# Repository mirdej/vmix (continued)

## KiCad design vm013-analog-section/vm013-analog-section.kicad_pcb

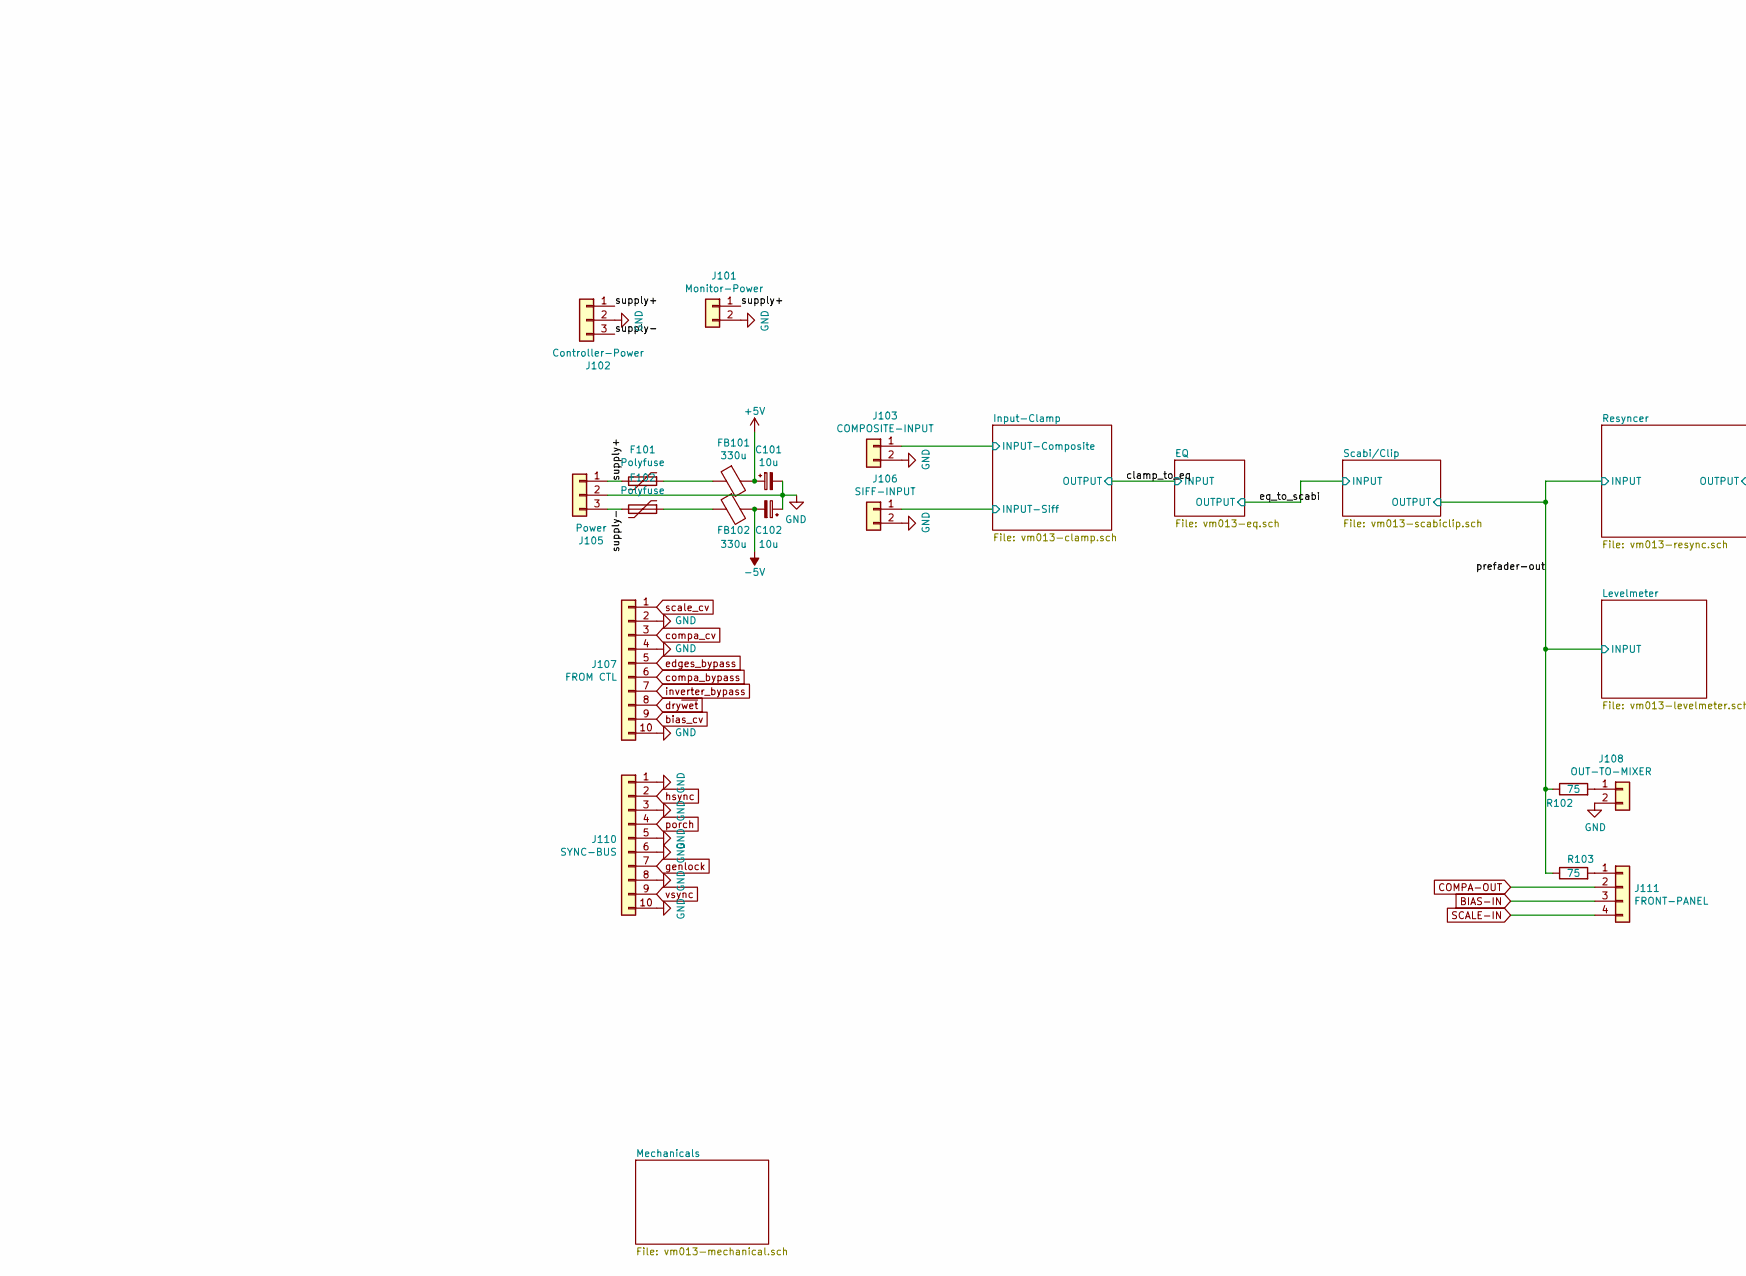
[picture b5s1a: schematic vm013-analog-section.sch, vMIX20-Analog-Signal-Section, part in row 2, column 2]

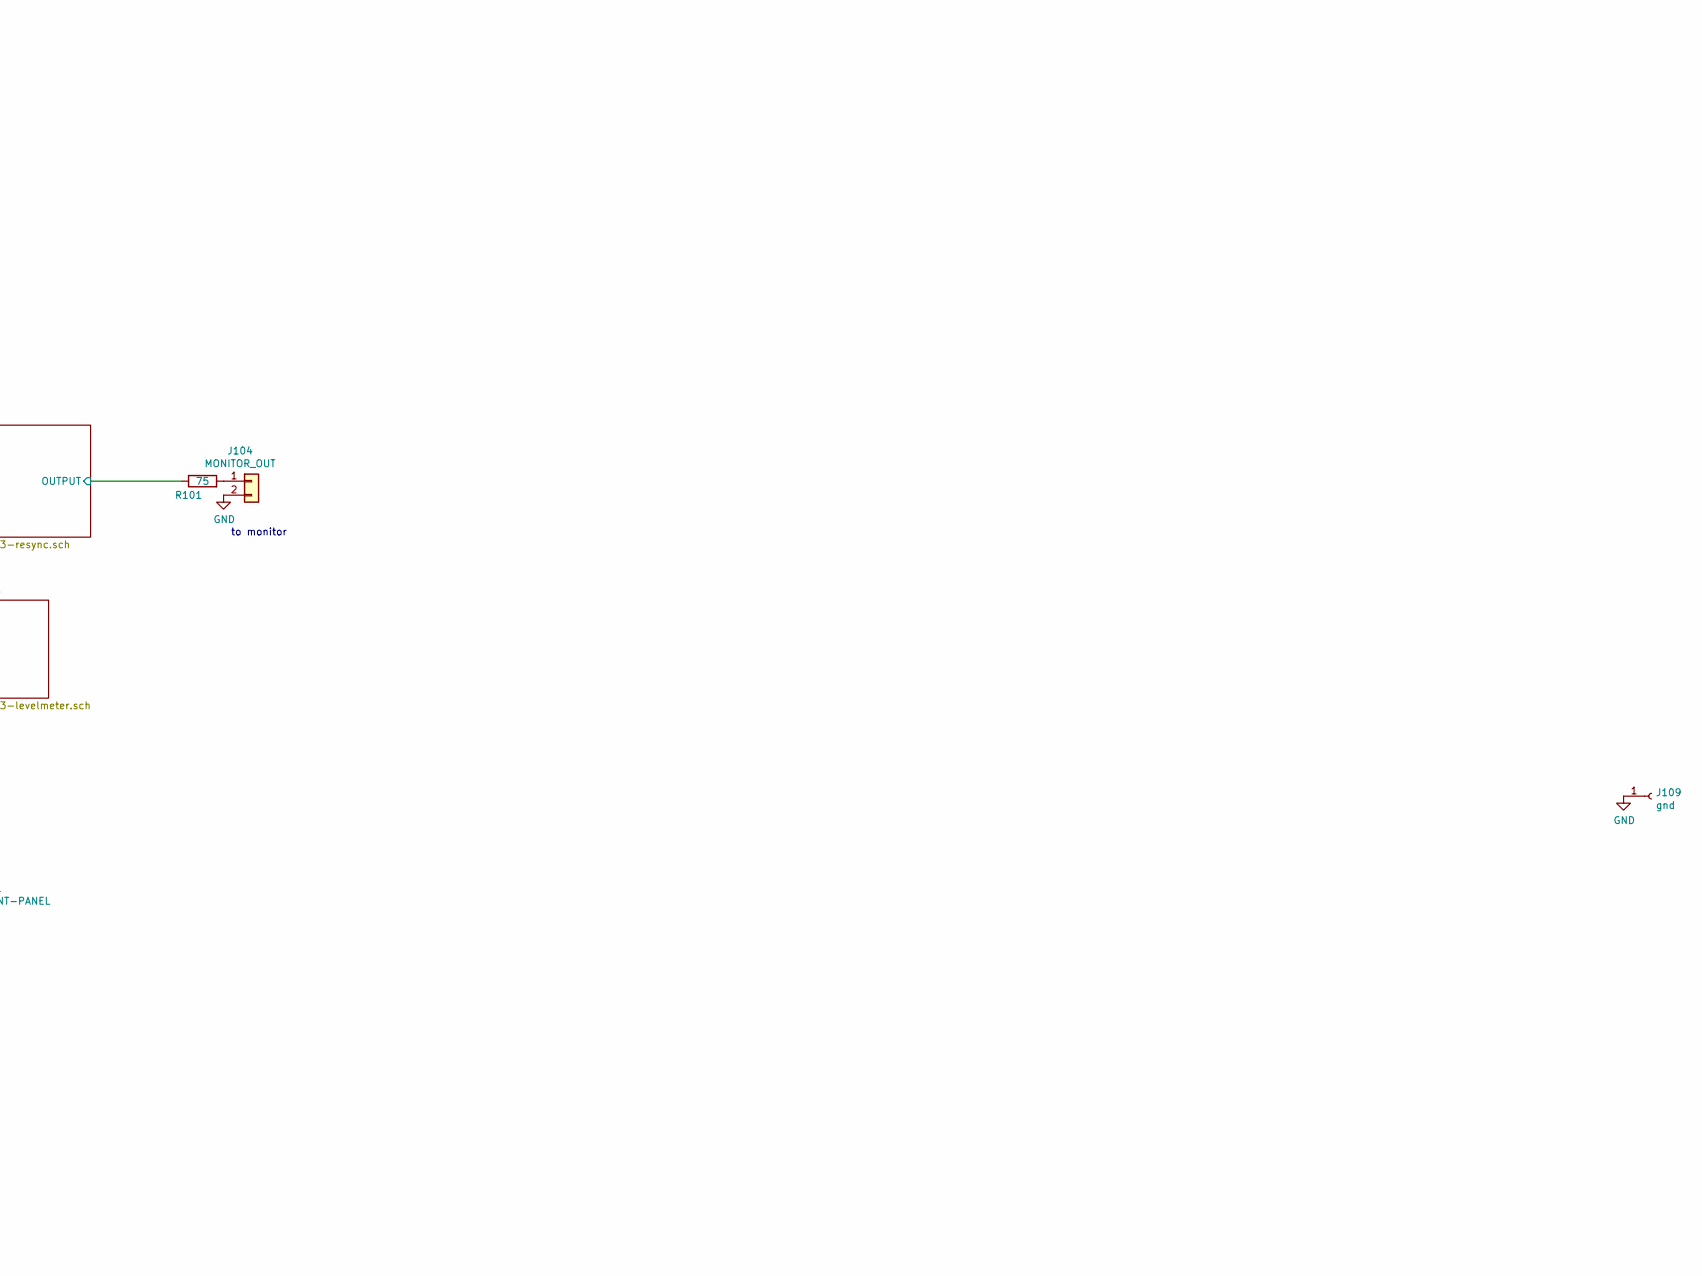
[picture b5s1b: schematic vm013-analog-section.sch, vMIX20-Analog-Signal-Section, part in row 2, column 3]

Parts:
C101, C102: 10u; CP_EIA-3528-21_Kemet-B_Pad1.50x2.35mm_HandSolder
F101, F102: Polyfuse; Fuse_0805_2012Metric
FB101, FB102: 330u; L_0805_2012Metric_Pad1.15x1.40mm_HandSolder
J101: Monitor-Power; Molex_KK-254_AE-6410-02A_1x02_P2.54mm_Vertical
J102: Controller-Power; Molex_KK-254_AE-6410-03A_1x03_P2.54mm_Vertical
J103: COMPOSITE-INPUT; Molex_KK-254_AE-6410-02A_1x02_P2.54mm_Vertical
J104: MONITOR_OUT; Molex_KK-254_AE-6410-02A_1x02_P2.54mm_Vertical
J105: Power; Molex_KK-254_AE-6410-03A_1x03_P2.54mm_Vertical
J106: SIFF-INPUT; Molex_KK-254_AE-6410-02A_1x02_P2.54mm_Vertical
J107: FROM CTL; IDC-Header_2x05_P2.54mm_Vertical
J108: OUT-TO-MIXER; Molex_KK-254_AE-6410-02A_1x02_P2.54mm_Vertical
J109: gnd; Solderpad_1mm
J110: SYNC-BUS; IDC-Header_2x05_P2.54mm_Vertical
J111: FRONT-PANEL; Molex_KK-254_AE-6410-04A_1x04_P2.54mm_Vertical
R101, R102, R103: 75; R_0805_2012Metric_Pad1.15x1.40mm_HandSolder

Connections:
+5V: C101.1, FB101.2; also elsewhere on the board
-5V: C102.2, FB102.2; also elsewhere on the board
/Input-Clamp/INPUT-Composite: J103.1; also elsewhere on the board
/Input-Clamp/INPUT-Siff: J106.1; also elsewhere on the board
/Resyncer/OUTPUT: R101.1; also elsewhere on the board
/prefader-out: R102.1, R103.1; also elsewhere on the board
/supply+: F101.2, J101.1, J102.1, J105.1
/supply-: F102.2, J102.3, J105.3
BIAS-IN: J111.3; also elsewhere on the board
COMPA-OUT: J111.2; also elsewhere on the board
GND: C101.2, C102.1, J101.2, J102.2, J103.2, J104.2, J105.2, J106.2, J107.2, J107.4, J107.10, J108.2, J109.1, J110.1, J110.3, J110.5, J110.6, J110.8, J110.10; also elsewhere on the board
unnamed: F101.1, FB101.1
unnamed: F102.1, FB102.1
unnamed: J104.1, R101.2
unnamed: J108.1, R102.2
unnamed: J111.1, R103.2
SCALE-IN: J111.4; also elsewhere on the board
bias_cv: J107.9; also elsewhere on the board
compa_bypass: J107.6; also elsewhere on the board
compa_cv: J107.3; also elsewhere on the board
dry~wet~: J107.8; also elsewhere on the board
edges_bypass: J107.5; also elsewhere on the board
genlock: J110.7; also elsewhere on the board
hsync: J110.2; also elsewhere on the board
inverter_bypass: J107.7; also elsewhere on the board
porch: J110.4; also elsewhere on the board
scale_cv: J107.1; also elsewhere on the board
vsync: J110.9; also elsewhere on the board

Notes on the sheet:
to monitor

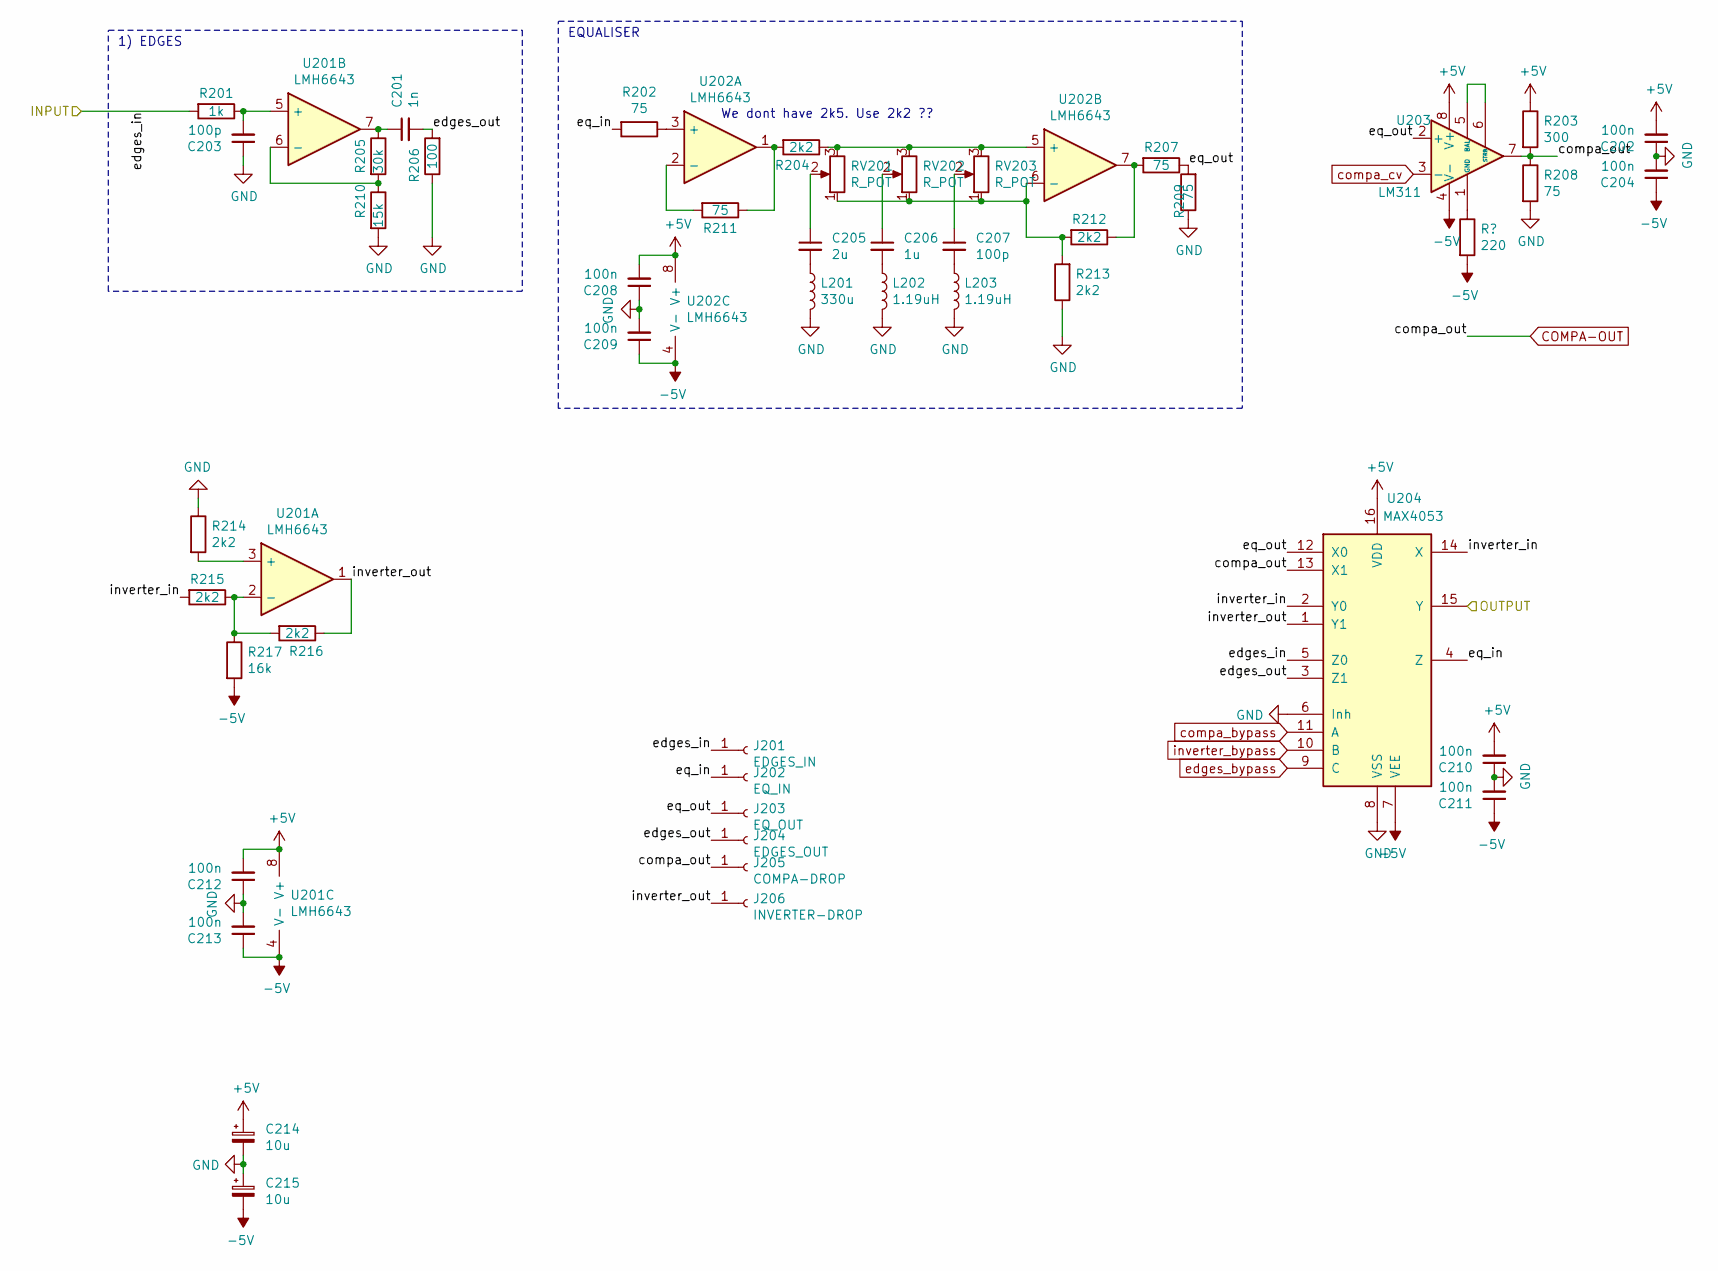
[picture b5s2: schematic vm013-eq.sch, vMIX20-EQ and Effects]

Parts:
C201: 1n; C_0805_2012Metric_Pad1.15x1.40mm_HandSolder
C202, C204, C208, C209, C210, C211, C212, C213: 100n; C_0603_1608Metric_Pad1.05x0.95mm_HandSolder
C203, C207: 100p; C_0805_2012Metric_Pad1.15x1.40mm_HandSolder
C205: 2u; C_1206_3216Metric_Pad1.42x1.75mm_HandSolder
C206: 1u; C_1206_3216Metric_Pad1.42x1.75mm_HandSolder
C214, C215: 10u; CP_EIA-3528-21_Kemet-B_Pad1.50x2.35mm_HandSolder
J201: EDGES_IN; Solderpad_1mm
J202: EQ_IN; Solderpad_1mm
J203: EQ_OUT; Solderpad_1mm
J204: EDGES_OUT; Solderpad_1mm
J205: COMPA-DROP; Solderpad_1mm
J206: INVERTER-DROP; Solderpad_1mm
L201: 330u; L_1210_3225Metric_Pad1.42x2.65mm_HandSolder
L202, L203: 1.19uH; L_1210_3225Metric_Pad1.42x2.65mm_HandSolder
R201: 1k; R_0805_2012Metric_Pad1.15x1.40mm_HandSolder
R202, R207, R208, R209, R211: 75; R_0805_2012Metric_Pad1.15x1.40mm_HandSolder
R203: 300; R_0805_2012Metric_Pad1.15x1.40mm_HandSolder
R204, R212, R213, R214, R215, R216: 2k2; R_0805_2012Metric_Pad1.15x1.40mm_HandSolder
R205: 30k; R_0805_2012Metric_Pad1.15x1.40mm_HandSolder
R206: 100; R_0805_2012Metric_Pad1.15x1.40mm_HandSolder
R210: 15k; R_0805_2012Metric_Pad1.15x1.40mm_HandSolder
R217: 16k; R_0805_2012Metric_Pad1.15x1.40mm_HandSolder
RV201, RV202, RV203: R_POT; Potentiometer_Alps_RK09K_Single_Horizontal
U201, U202: LMH6643; SOIC-8_3.9x4.9mm_P1.27mm
U203: LM311; SOIC-8_3.9x4.9mm_P1.27mm
U204: MAX4053; SOP-16_4.55x10.3mm_P1.27mm

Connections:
+5V: C202.2, C208.2, C210.2, C212.2, C214.1, R203.1, U201.8 (V+), U202.8 (V+), U203.8 (V+), U204.16 (VDD); also elsewhere on the board
-5V: C204.1, C209.1, C211.1, C213.1, C215.2, R217.2, U201.4 (V-), U202.4 (V-), U203.4 (V-), U204.7 (VEE); also elsewhere on the board
/EQ/edges_out: C201.2, J204.1, R206.2, U204.3 (Z1)
/EQ/eq_in: J202.1, R202.2, U204.4 (Z)
/EQ/eq_out: J203.1, R207.1, R209.2, U203.2 (+), U204.12 (X0)
/EQ/inverter_in: R215.2, U204.2 (Y0), U204.14 (X)
/EQ/inverter_out: J206.1, R216.1, U201.1, U204.1 (Y1)
/clamp_to_eq: J201.1, R201.2, U204.5 (Z0); also elsewhere on the board
/eq_to_scabi: U204.15 (Y); also elsewhere on the board
COMPA-OUT: J205.1, R203.2, R208.1, U203.7, U204.13 (X1); also elsewhere on the board
GND: C202.1, C203.1, C204.2, C208.1, C209.2, C210.1, C211.2, C212.1, C213.2, C214.2, C215.1, L201.2, L202.2, L203.2, R206.1, R208.2, R209.1, R210.2, R213.1, R214.1, U203.1 (GND), U204.6 (Inh), U204.8 (VSS); also elsewhere on the board
unnamed: C201.1, R205.1, U201.7
unnamed: C203.2, R201.1, U201.5 (+)
unnamed: C205.1, RV201.2
unnamed: C205.2, L201.1
unnamed: C206.1, RV202.2
unnamed: C206.2, L202.1
unnamed: C207.1, RV203.2
unnamed: C207.2, L203.1
unnamed: R202.1, U202.3 (+)
unnamed: R204.1, RV201.3, RV202.3, RV203.3, U202.5 (+)
unnamed: R204.2, R211.1, U202.1
unnamed: R205.2, R210.1, U201.6 (-)
unnamed: R207.2, R212.1, U202.7
unnamed: R211.2, U202.2 (-)
unnamed: R212.2, R213.2, RV201.1, RV202.1, RV203.1, U202.6 (-)
unnamed: R214.2, U201.3 (+)
unnamed: R215.1, R216.2, R217.1, U201.2 (-)
unnamed: U203.5 (BAL), U203.6 (STRB)
compa_bypass: U204.11 (A); also elsewhere on the board
compa_cv: U203.3 (-); also elsewhere on the board
edges_bypass: U204.9 (C); also elsewhere on the board
inverter_bypass: U204.10 (B); also elsewhere on the board

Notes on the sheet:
EQUALISER
We dont have 2k5. Use 2k2 ??
1) EDGES

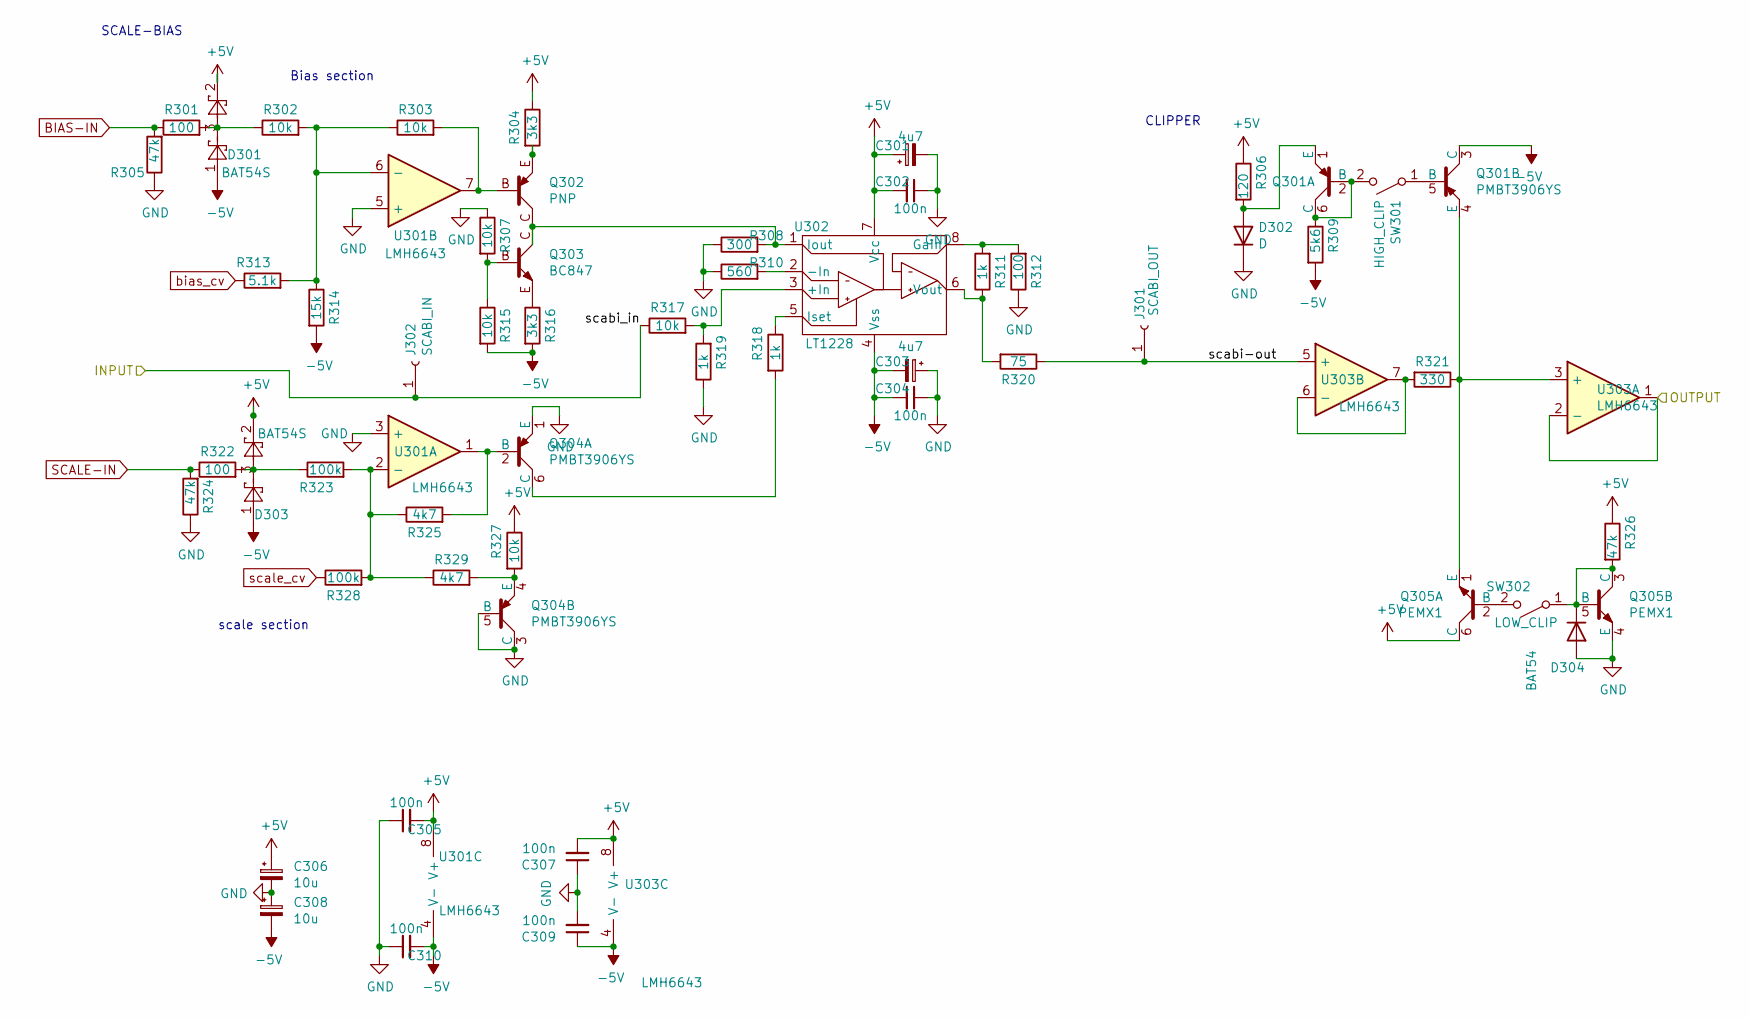
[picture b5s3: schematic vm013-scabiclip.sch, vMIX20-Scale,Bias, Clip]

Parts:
C301, C303: 4u7; CP_EIA-3528-21_Kemet-B_Pad1.50x2.35mm_HandSolder
C302, C304, C305, C307, C309, C310: 100n; C_0603_1608Metric_Pad1.05x0.95mm_HandSolder
C306, C308: 10u; CP_EIA-3528-21_Kemet-B_Pad1.50x2.35mm_HandSolder
D301, D303: BAT54S; SOT-23
D302: D; D_MiniMELF
D304: BAT54; D_SOT-23_ANK
J301: SCABI_OUT; Solderpad_1mm
J302: SCABI_IN; Solderpad_1mm
Q301, Q304: PMBT3906YS; SOT-363_SC-70-6_Handsoldering
Q302: PNP; SOT-23_BEC
Q303: BC847; SOT-23_BEC
Q305: PEMX1; SOT-666
R301, R312, R322: 100; R_0805_2012Metric_Pad1.15x1.40mm_HandSolder
R302, R303, R307, R315, R317, R327: 10k; R_0805_2012Metric_Pad1.15x1.40mm_HandSolder
R304, R316: 3k3; R_0805_2012Metric_Pad1.15x1.40mm_HandSolder
R305, R324, R326: 47k; R_0805_2012Metric_Pad1.15x1.40mm_HandSolder
R306: 120; R_0805_2012Metric_Pad1.15x1.40mm_HandSolder
R308: 300; R_0805_2012Metric_Pad1.15x1.40mm_HandSolder
R309: 5k6; R_0805_2012Metric_Pad1.15x1.40mm_HandSolder
R310: 560; R_0805_2012Metric_Pad1.15x1.40mm_HandSolder
R311, R318, R319: 1k; R_0805_2012Metric_Pad1.15x1.40mm_HandSolder
R313: 5.1k; R_0805_2012Metric_Pad1.15x1.40mm_HandSolder
R314: 15k; R_0805_2012Metric_Pad1.15x1.40mm_HandSolder
R320: 75; R_0805_2012Metric_Pad1.15x1.40mm_HandSolder
R321: 330; R_0805_2012Metric_Pad1.15x1.40mm_HandSolder
R323, R328: 100k; R_0805_2012Metric_Pad1.15x1.40mm_HandSolder
R325, R329: 4k7; R_0805_2012Metric_Pad1.15x1.40mm_HandSolder
SW301: HIGH_CLIP; Molex_KK-254_AE-6410-02A_1x02_P2.54mm_Vertical
SW302: LOW_CLIP; Molex_KK-254_AE-6410-02A_1x02_P2.54mm_Vertical
U301, U303: LMH6643; SOIC-8_3.9x4.9mm_P1.27mm
U302: LT1228; SOIC-8_3.9x4.9mm_P1.27mm

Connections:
+5V: C301.1, C302.2, C305.2, C306.1, C307.2, D301.2, D303.2, Q305.6 (C), R304.1, R306.1, R326.1, R327.1, U301.8 (V+), U302.7 (Vcc), U303.8 (V+); also elsewhere on the board
-5V: C303.2, C304.2, C308.2, C309.1, C310.2, D301.1, D303.1, Q301.3 (C), R309.2, R314.2, R315.2, R316.2, U301.4 (V-), U302.4 (Vss), U303.4 (V-); also elsewhere on the board
/Scabi/Clip/scabi-out: J301.1, R320.1, U303.5 (+)
/eq_to_scabi: J302.1, R317.1; also elsewhere on the board
/prefader-out: U303.1, U303.2 (-); also elsewhere on the board
BIAS-IN: R301.1, R305.2; also elsewhere on the board
GND: C301.2, C302.1, C303.1, C304.1, C305.1, C306.2, C307.1, C308.1, C309.2, C310.1, D302.1 (K), D304.2 (A), Q304.1 (E), Q304.3 (C), Q304.5 (B), Q305.4 (E), R305.1, R307.1, R308.1, R310.1, R312.1, R319.1, R324.1, U301.3 (+), U301.5 (+); also elsewhere on the board
unnamed: D301.3, R301.2, R302.1
unnamed: D302.2 (A), Q301.1 (E), R306.2
unnamed: D303.3, R322.2, R323.1
unnamed: D304.1 (K), Q305.3 (C), Q305.5 (B), R326.2, SW302.1 (A)
unnamed: Q301.2 (B), Q301.6 (C), R309.1, SW301.2 (B)
unnamed: Q301.4 (E), Q305.1 (E), R321.1, U303.3 (+)
unnamed: Q301.5 (B), SW301.1 (A)
unnamed: Q302.B, R303.2, U301.7
unnamed: Q302.C, Q303.C, R308.2, U302.1 (Iout)
unnamed: Q302.E, R304.2
unnamed: Q303.B, R307.2, R315.1
unnamed: Q303.E, R316.1
unnamed: Q304.2 (B), R325.2, U301.1
unnamed: Q304.4 (E), R327.2, R329.2
unnamed: Q304.6 (C), R318.2
unnamed: Q305.2 (B), SW302.2 (B)
unnamed: R302.2, R303.1, R313.2, R314.1, U301.6 (-)
unnamed: R310.2, U302.2 (-In)
unnamed: R311.1, R320.2, U302.6 (Vout)
unnamed: R311.2, R312.2, U302.8 (Gain)
unnamed: R317.2, R319.2, U302.3 (+In)
unnamed: R318.1, U302.5 (Iset)
unnamed: R321.2, U303.6 (-), U303.7
unnamed: R323.2, R325.1, R328.2, R329.1, U301.2 (-)
SCALE-IN: R322.1, R324.2; also elsewhere on the board
bias_cv: R313.1; also elsewhere on the board
scale_cv: R328.1; also elsewhere on the board

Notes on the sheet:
Bias section
scale section
SCALE-BIAS
CLIPPER

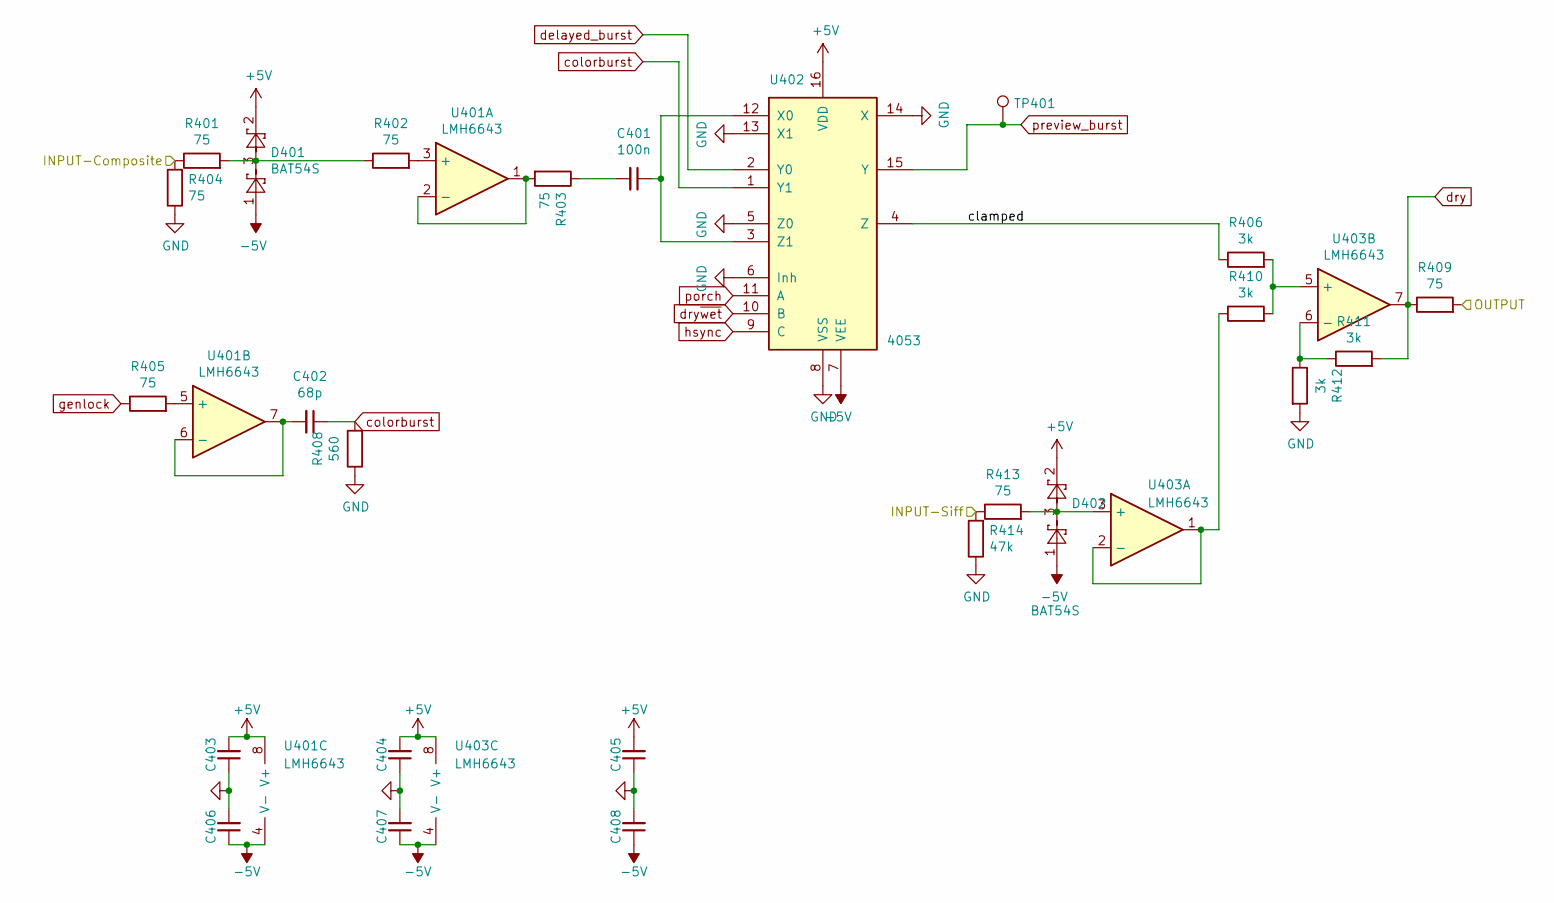
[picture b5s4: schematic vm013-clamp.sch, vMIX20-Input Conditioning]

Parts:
C401, C403, C404, C405, C406, C407, C408: 100n; C_0603_1608Metric_Pad1.05x0.95mm_HandSolder
C402: 68p; C_1206_3216Metric_Pad1.42x1.75mm_HandSolder
D401, D402: BAT54S; SOT-23
R401, R402, R403, R404, R405, R409, R413: 75; R_0805_2012Metric_Pad1.15x1.40mm_HandSolder
R406, R410, R411, R412: 3k; R_0805_2012Metric_Pad1.15x1.40mm_HandSolder
R408: 560; R_0805_2012Metric_Pad1.15x1.40mm_HandSolder
R414: 47k; R_0805_2012Metric_Pad1.15x1.40mm_HandSolder
TP401: TestPoint; Solderpad_1mm
U401, U403: LMH6643; SOIC-8_3.9x4.9mm_P1.27mm
U402: 4053; SOIC-16_3.9x9.9mm_P1.27mm

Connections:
+5V: C403.2, C404.2, C405.2, D401.2, D402.2, U401.8 (V+), U402.16 (VDD), U403.8 (V+); also elsewhere on the board
-5V: C406.1, C407.1, C408.1, D401.1, D402.1, U401.4 (V-), U402.7 (VEE), U403.4 (V-); also elsewhere on the board
/Input-Clamp/INPUT-Composite: R401.1, R404.2; also elsewhere on the board
/Input-Clamp/INPUT-Siff: R413.1, R414.2; also elsewhere on the board
/Input-Clamp/clamped: R406.1, U402.4 (Z)
/clamp_to_eq: R409.2; also elsewhere on the board
GND: C403.1, C404.1, C405.1, C406.2, C407.2, C408.2, R404.1, R408.1, R412.2, R414.1, U402.5 (Z0), U402.6 (Inh), U402.8 (VSS), U402.13 (X1), U402.14 (X); also elsewhere on the board
unnamed: C401.1, U402.3 (Z1), U402.12 (X0)
unnamed: C401.2, R403.1
unnamed: C402.2, U401.6 (-), U401.7
unnamed: D401.3, R401.2, R402.1
unnamed: D402.3, R413.2, U403.3 (+)
unnamed: R402.2, U401.3 (+)
unnamed: R403.2, U401.1, U401.2 (-)
unnamed: R405.2, U401.5 (+)
unnamed: R406.2, R410.2, U403.5 (+)
unnamed: R410.1, U403.1, U403.2 (-)
unnamed: R411.1, R412.1, U403.6 (-)
colorburst: C402.1, R408.2, U402.1 (Y1); also elsewhere on the board
delayed_burst: U402.2 (Y0); also elsewhere on the board
dry: R409.1, R411.2, U403.7; also elsewhere on the board
dry~wet~: U402.10 (B); also elsewhere on the board
genlock: R405.1; also elsewhere on the board
hsync: U402.9 (C); also elsewhere on the board
porch: U402.11 (A); also elsewhere on the board
preview_burst: TP401.1, U402.15 (Y); also elsewhere on the board

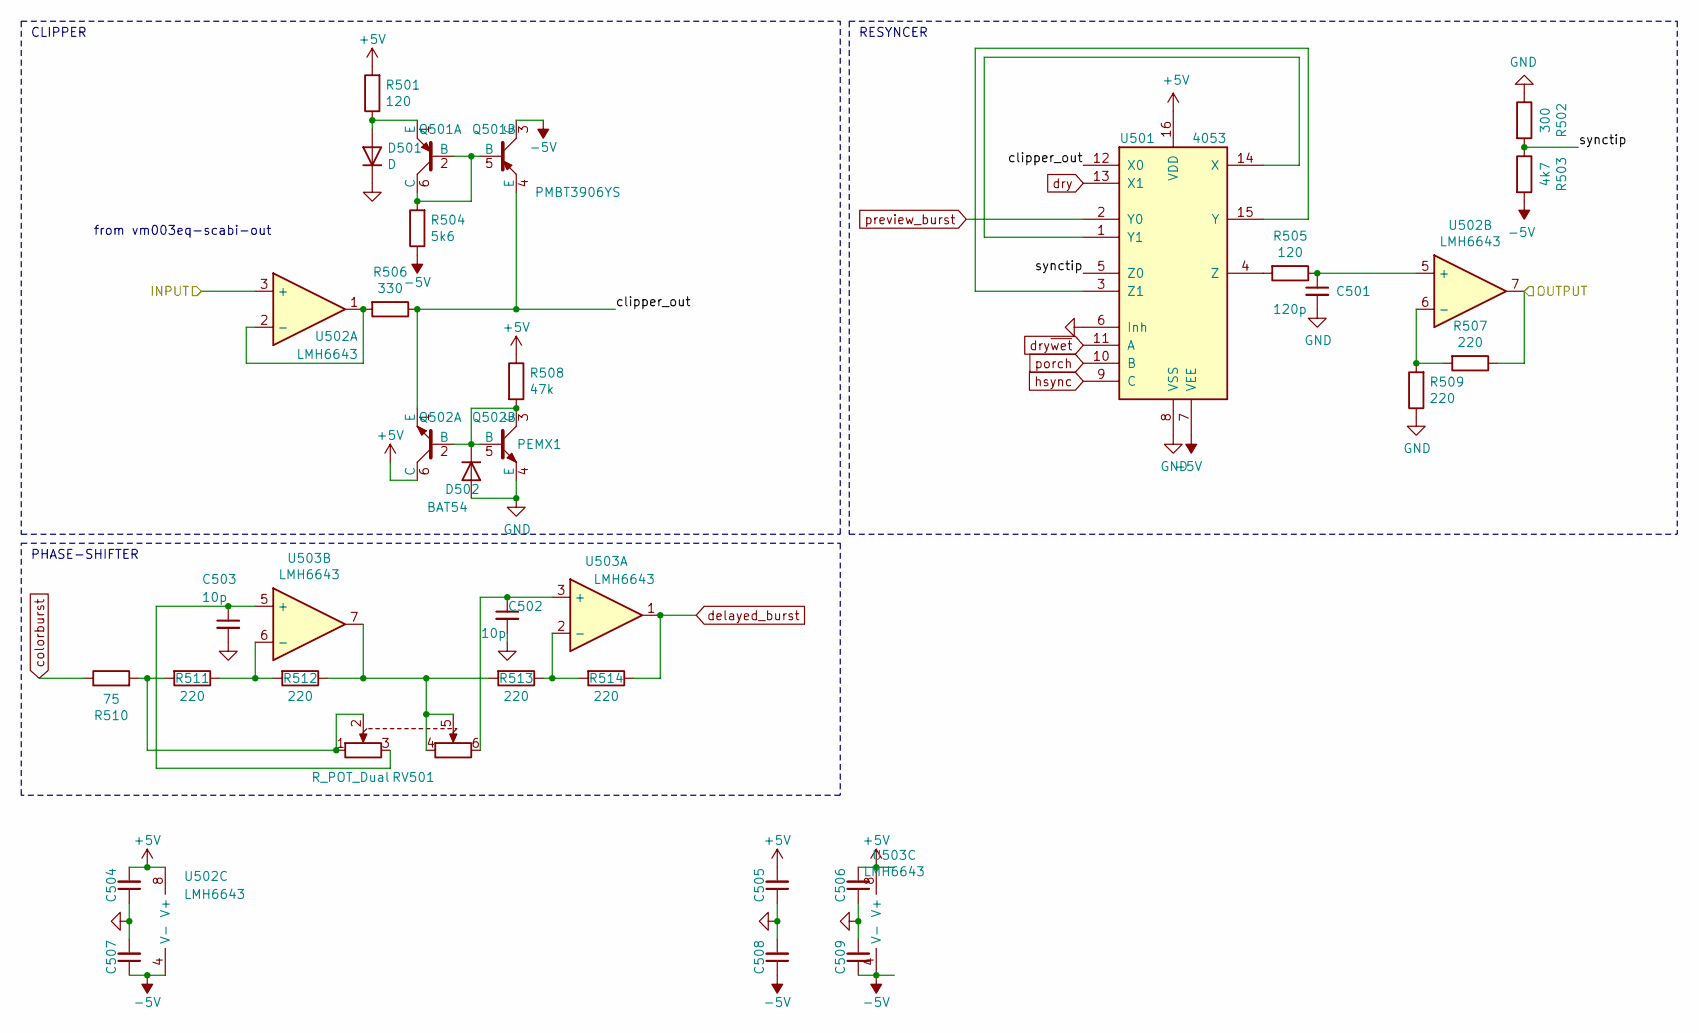
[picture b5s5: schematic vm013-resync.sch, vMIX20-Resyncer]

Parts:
C501: 120p; C_0805_2012Metric_Pad1.15x1.40mm_HandSolder
C502, C503: 10p; C_0805_2012Metric_Pad1.15x1.40mm_HandSolder
C504, C505, C506, C507, C508, C509: 100n; C_0603_1608Metric_Pad1.05x0.95mm_HandSolder
D501: D; D_MiniMELF
D502: BAT54; D_SOT-23_ANK
Q501: PMBT3906YS; SOT-363_SC-70-6_Handsoldering
Q502: PEMX1; SOT-666
R501, R505: 120; R_0805_2012Metric_Pad1.15x1.40mm_HandSolder
R502: 300; R_0805_2012Metric_Pad1.15x1.40mm_HandSolder
R503: 4k7; R_0805_2012Metric_Pad1.15x1.40mm_HandSolder
R504: 5k6; R_0805_2012Metric_Pad1.15x1.40mm_HandSolder
R506: 330; R_0805_2012Metric_Pad1.15x1.40mm_HandSolder
R507, R509, R511, R512, R513, R514: 220; R_0805_2012Metric_Pad1.15x1.40mm_HandSolder
R508: 47k; R_0805_2012Metric_Pad1.15x1.40mm_HandSolder
R510: 75; R_0805_2012Metric_Pad1.15x1.40mm_HandSolder
RV501: R_POT_Dual; RK12L123
U501: 4053; SOIC-16_3.9x9.9mm_P1.27mm
U502, U503: LMH6643; SOIC-8_3.9x4.9mm_P1.27mm

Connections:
+5V: C504.2, C505.2, C506.2, Q502.6 (C), R501.2, R508.1, U501.16 (VDD), U502.8 (V+), U503.8 (V+); also elsewhere on the board
-5V: C507.1, C508.1, C509.1, Q501.3 (C), R503.2, R504.1, U501.7 (VEE), U502.4 (V-), U503.4 (V-); also elsewhere on the board
/Resyncer/OUTPUT: R507.1, U502.7; also elsewhere on the board
/Resyncer/clipper_out: Q501.4 (E), Q502.1 (E), R506.1, U501.12 (X0)
/Resyncer/synctip: R502.2, R503.1, U501.5 (Z0)
/prefader-out: U502.3 (+); also elsewhere on the board
GND: C501.2, C502.2, C503.2, C504.1, C505.1, C506.1, C507.2, C508.2, C509.2, D501.1 (K), D502.2 (A), Q502.4 (E), R502.1, R509.1, U501.6 (Inh), U501.8 (VSS); also elsewhere on the board
unnamed: C501.1, R505.1, U502.5 (+)
unnamed: C502.1, RV501.6, U503.3 (+)
unnamed: C503.1, RV501.3, U503.5 (+)
unnamed: D501.2 (A), Q501.1 (E), R501.1
unnamed: D502.1 (K), Q502.2 (B), Q502.3 (C), Q502.5 (B), R508.2
unnamed: Q501.2 (B), Q501.5 (B), Q501.6 (C), R504.2
unnamed: R505.2, U501.4 (Z)
unnamed: R506.2, U502.1, U502.2 (-)
unnamed: R507.2, R509.2, U502.6 (-)
unnamed: R510.2, R511.2, RV501.1, RV501.2
unnamed: R511.1, R512.2, U503.6 (-)
unnamed: R512.1, R513.2, RV501.4, RV501.5, U503.7
unnamed: R513.1, R514.2, U503.2 (-)
unnamed: U501.1 (Y1), U501.14 (X)
unnamed: U501.3 (Z1), U501.15 (Y)
colorburst: R510.1; also elsewhere on the board
delayed_burst: R514.1, U503.1; also elsewhere on the board
dry: U501.13 (X1); also elsewhere on the board
dry~wet~: U501.11 (A); also elsewhere on the board
hsync: U501.9 (C); also elsewhere on the board
porch: U501.10 (B); also elsewhere on the board
preview_burst: U501.2 (Y0); also elsewhere on the board

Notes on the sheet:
PHASE-SHIFTER
CLIPPER
RESYNCER
from vm003eq-scabi-out

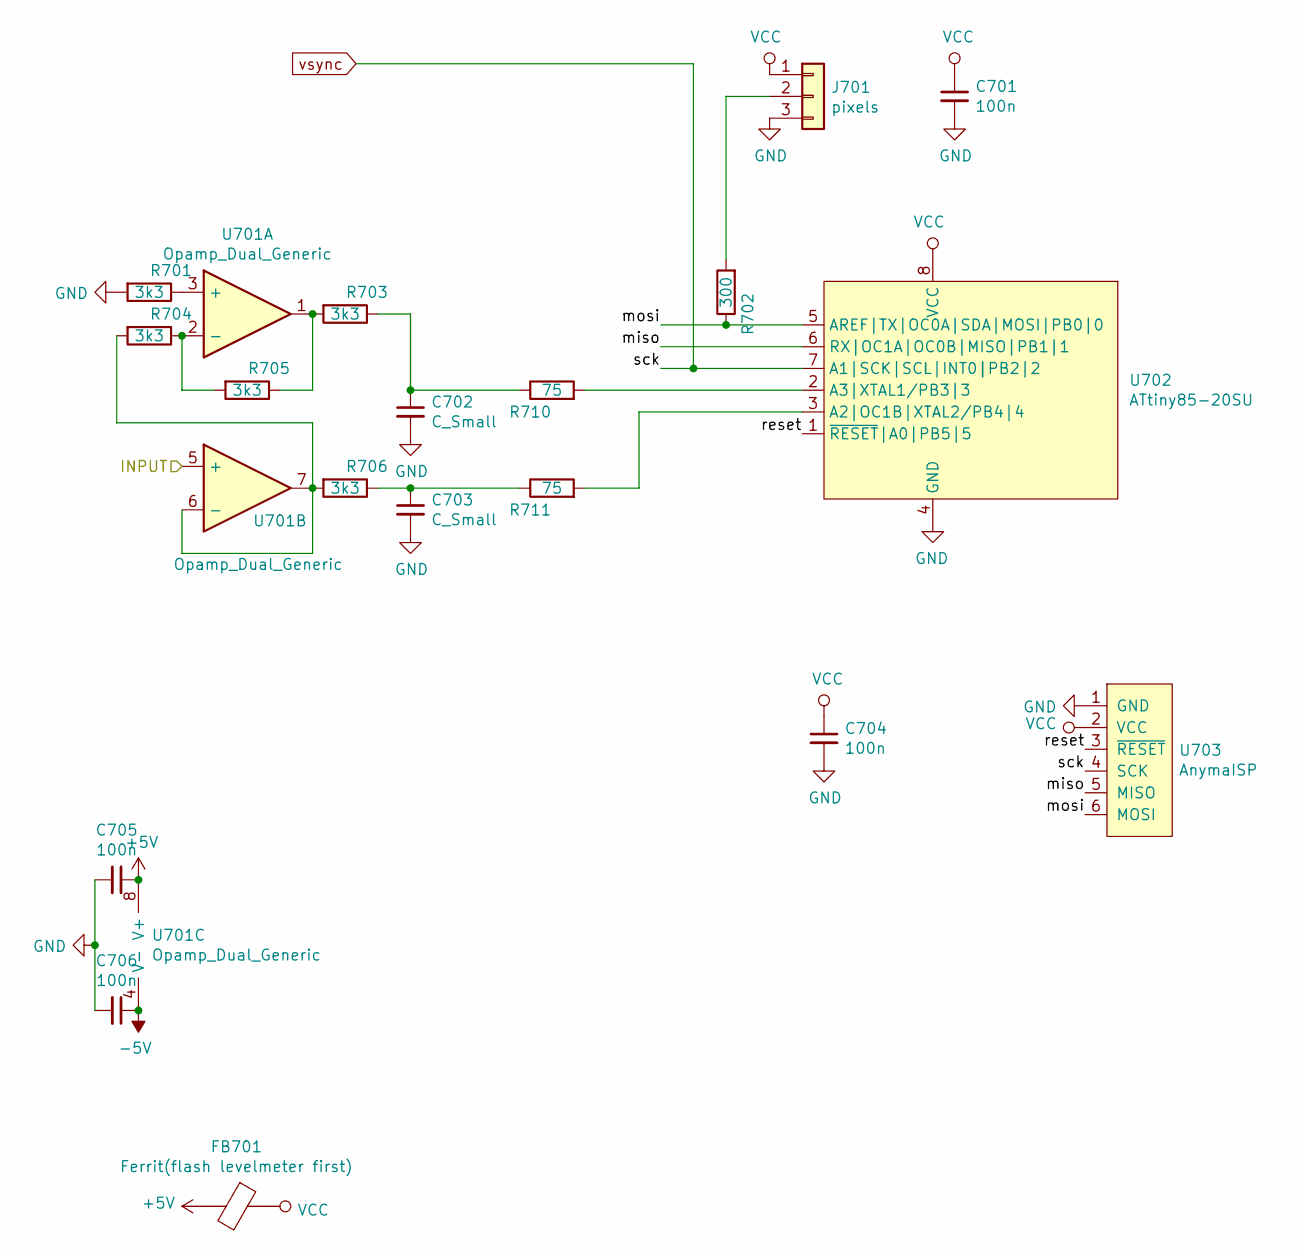
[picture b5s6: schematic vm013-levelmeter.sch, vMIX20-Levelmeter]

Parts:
C701, C704, C705, C706: 100n; C_0603_1608Metric_Pad1.05x0.95mm_HandSolder
C702, C703: C_Small; C_0603_1608Metric_Pad1.05x0.95mm_HandSolder
FB701: Ferrit(flash levelmeter first); L_0805_2012Metric_Pad1.15x1.40mm_HandSolder
J701: pixels; Molex_KK-254_AE-6410-03A_1x03_P2.54mm_Vertical
R701, R703, R704, R705, R706: 3k3; R_0805_2012Metric_Pad1.15x1.40mm_HandSolder
R702: 300; R_0805_2012Metric_Pad1.15x1.40mm_HandSolder
R710, R711: 75; R_0805_2012Metric_Pad1.15x1.40mm_HandSolder
U701: Opamp_Dual_Generic; SOIC-8_3.9x4.9mm_P1.27mm
U702: ATtiny85-20SU; SOIJ-8_5.3x5.3mm_P1.27mm
U703: AnymaISP; PinHeader_1x06_P2.54mm_Vertical

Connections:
+5V: C705.1, FB701.2, U701.8 (V+); also elsewhere on the board
-5V: C706.1, U701.4 (V-); also elsewhere on the board
/Levelmeter/miso: U702.6 (RX|OC1A|OC0B|MISO|PB1|1), U703.5 (MISO)
/Levelmeter/mosi: R702.1, U702.5 (AREF|TX|OC0A|SDA|MOSI|PB0|0), U703.6 (MOSI)
/Levelmeter/reset: U702.1 (~RESET~|A0|PB5|5), U703.3 (~RESET)
/prefader-out: U701.5 (+); also elsewhere on the board
GND: C701.2, C702.2, C703.2, C704.2, C705.2, C706.2, J701.3, R701.2, U702.4 (GND), U703.1 (GND); also elsewhere on the board
unnamed: C702.1, R703.1, R710.1
unnamed: C703.1, R706.1, R711.1
unnamed: J701.2, R702.2
unnamed: R701.1, U701.3 (+)
unnamed: R703.2, R705.1, U701.1
unnamed: R704.1, R705.2, U701.2 (-)
unnamed: R704.2, R706.2, U701.6 (-), U701.7
unnamed: R710.2, U702.2 (A3|XTAL1/PB3|3)
unnamed: R711.2, U702.3 (A2|OC1B|XTAL2/PB4|4)
VCC: C701.1, C704.1, FB701.1, J701.1, U702.8 (VCC), U703.2 (VCC)
vsync: U702.7 (A1|SCK|SCL|INT0|PB2|2), U703.4 (SCK); also elsewhere on the board
